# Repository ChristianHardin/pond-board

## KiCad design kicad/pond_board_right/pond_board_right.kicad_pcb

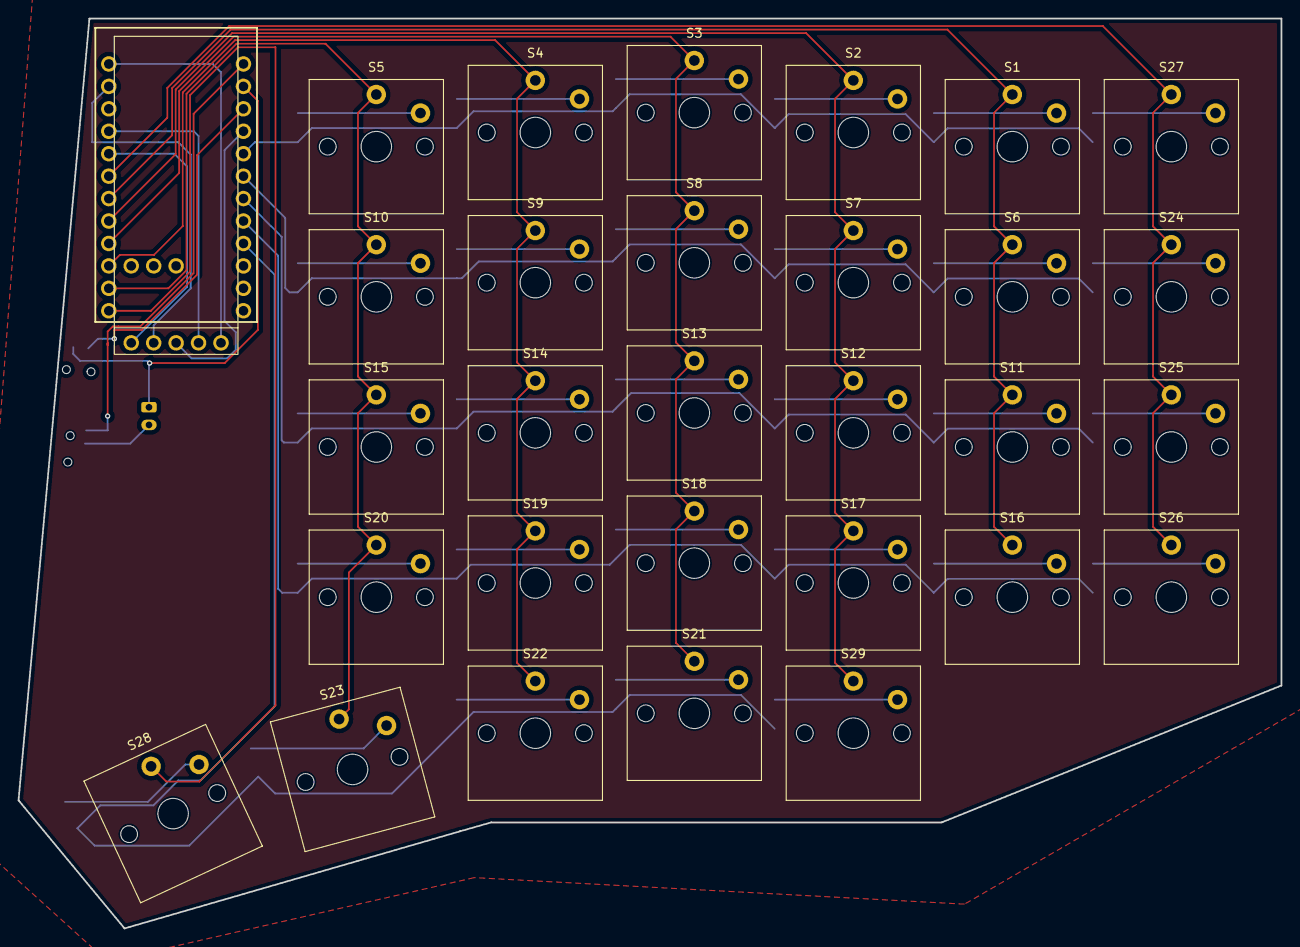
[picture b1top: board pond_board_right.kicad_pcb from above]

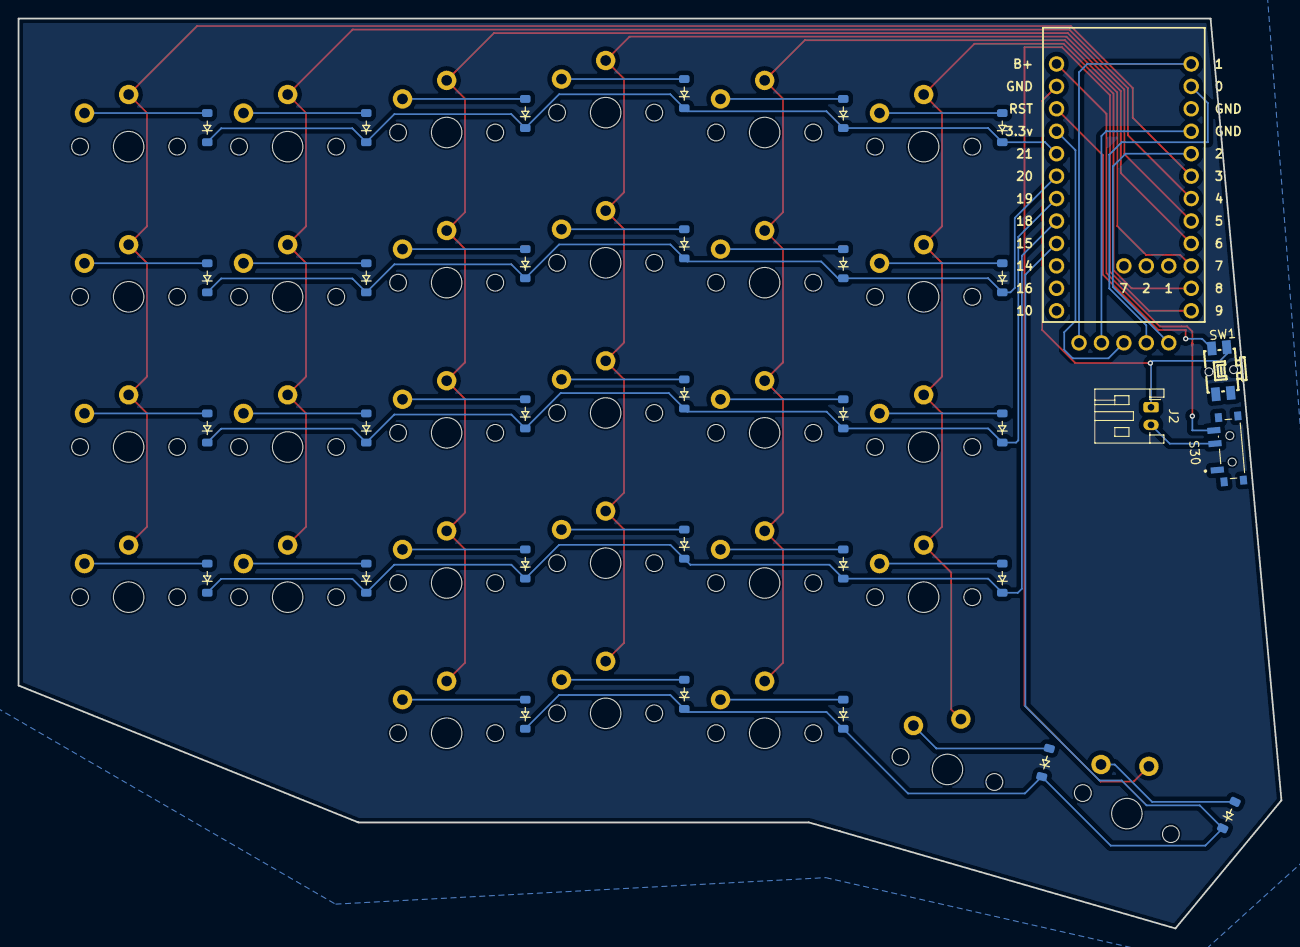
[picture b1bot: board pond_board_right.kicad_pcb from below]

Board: 2 copper layers, 143.0 x 103.0 mm, 63 parts (32 on the bottom side), 50 nets.

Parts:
D1, D2, D3, D4, D5, D6, D7, D8, D9, D10, D11, D12, D13, D14, D15, D16, D17, D18, D19, D20, D21, D22, D23, D24, D25, D26, D27, D28, D29: Diode; Diode_SOD-123
J1: Conn_01x05_Socket; Nice!View
J2: Conn_01x02; JST_PH_S2B-PH-K_1x02_P2.00mm_Horizontal
S1, S2, S3, S4, S5, S6, S7, S8, S9, S10, S11, S12, S13, S14, S15, S16, S17, S18, S19, S20, S21, S22, S23, S24, S25, S26, S27, S28, S29: Keyswitch; Choc_V1_1.00u
S30: SSSS811101; SW_SSSS811101
SW1: EVQPUC02K
U3: Nice_Nano_V2

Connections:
CS: J1.5, U3.1
MOSI: J1.1, U3.5 (2)
unnamed: D1.2 (A), S1.2
unnamed: D2.2 (A), S2.2
unnamed: D3.2 (A), S3.2
unnamed: D4.2 (A), S4.2
unnamed: D5.2 (A), S5.2
unnamed: D6.2 (A), S11.2
unnamed: D7.2 (A), S12.2
unnamed: D8.2 (A), S13.2
unnamed: D9.2 (A), S14.2
unnamed: D10.2 (A), S15.2
unnamed: D11.2 (A), S6.2
unnamed: D12.2 (A), S7.2
unnamed: D13.2 (A), S8.2
unnamed: D14.2 (A), S9.2
unnamed: D15.2 (A), S10.2
unnamed: D16.2 (A), S16.2
unnamed: D17.2 (A), S17.2
unnamed: D18.2 (A), S18.2
unnamed: D19.2 (A), S19.2
unnamed: D20.2 (A), S20.2
unnamed: D21.2 (A), S21.2
unnamed: D22.2 (A), S22.2
unnamed: D23.2 (A), S23.2
unnamed: D24.2 (A), S24.2
unnamed: D25.2 (A), S25.2
unnamed: D26.2 (A), S26.2
unnamed: D27.2 (A), S27.2
unnamed: D28.2 (A), S28.2
unnamed: D29.2 (A), S29.2
SCK: J1.2, U3.2 (0)
bat+: J2.2, S30.2
col0: S24.1, S25.1, S26.1, S27.1, U3.6 (3)
col1: S1.1, S6.1, S11.1, S16.1, U3.7 (4)
col2: S2.1, S7.1, S12.1, S17.1, S29.1, U3.8 (5)
col3: S3.1, S8.1, S13.1, S18.1, S21.1, U3.9 (6)
col4: S4.1, S9.1, S14.1, S19.1, S22.1, U3.10 (7)
col5: S5.1, S10.1, S15.1, S20.1, S23.1, U3.11 (8)
col6: S28.1, U3.12 (9)
gnd: J2.1, SW1.2, U3.23 (GND)
nano+: S30.3, U3.24 (B+)
reset: SW1.1, U3.22 (RST)
row0: D1.1 (K), D2.1 (K), D3.1 (K), D4.1 (K), D5.1 (K), D27.1 (K), U3.20 (21)
row1: D11.1 (K), D12.1 (K), D13.1 (K), D14.1 (K), D15.1 (K), D24.1 (K), U3.19 (20)
row2: D6.1 (K), D7.1 (K), D8.1 (K), D9.1 (K), D10.1 (K), D25.1 (K), U3.18 (19)
row3: D16.1 (K), D17.1 (K), D18.1 (K), D19.1 (K), D20.1 (K), D26.1 (K), U3.17 (18)
row4: D21.1 (K), D22.1 (K), D23.1 (K), D28.1 (K), D29.1 (K), U3.16 (15)
view_gnd: J1.4, U3.4 (GND)
view_pwr: J1.3, U3.21 (3.3v)

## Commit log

2024-11-21 init commit
